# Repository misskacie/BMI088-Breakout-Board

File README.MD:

# Breakout Board for BMI088 Accelerometer/Gyroscrope
Provides breakouts for all pins, 2 headers for the I2C wires to allow daisy chaining, address selection jumper, mode select jumper, the option to bridge VDD and VDDIO as the supply voltage range overlaps for 3.3v logic level.

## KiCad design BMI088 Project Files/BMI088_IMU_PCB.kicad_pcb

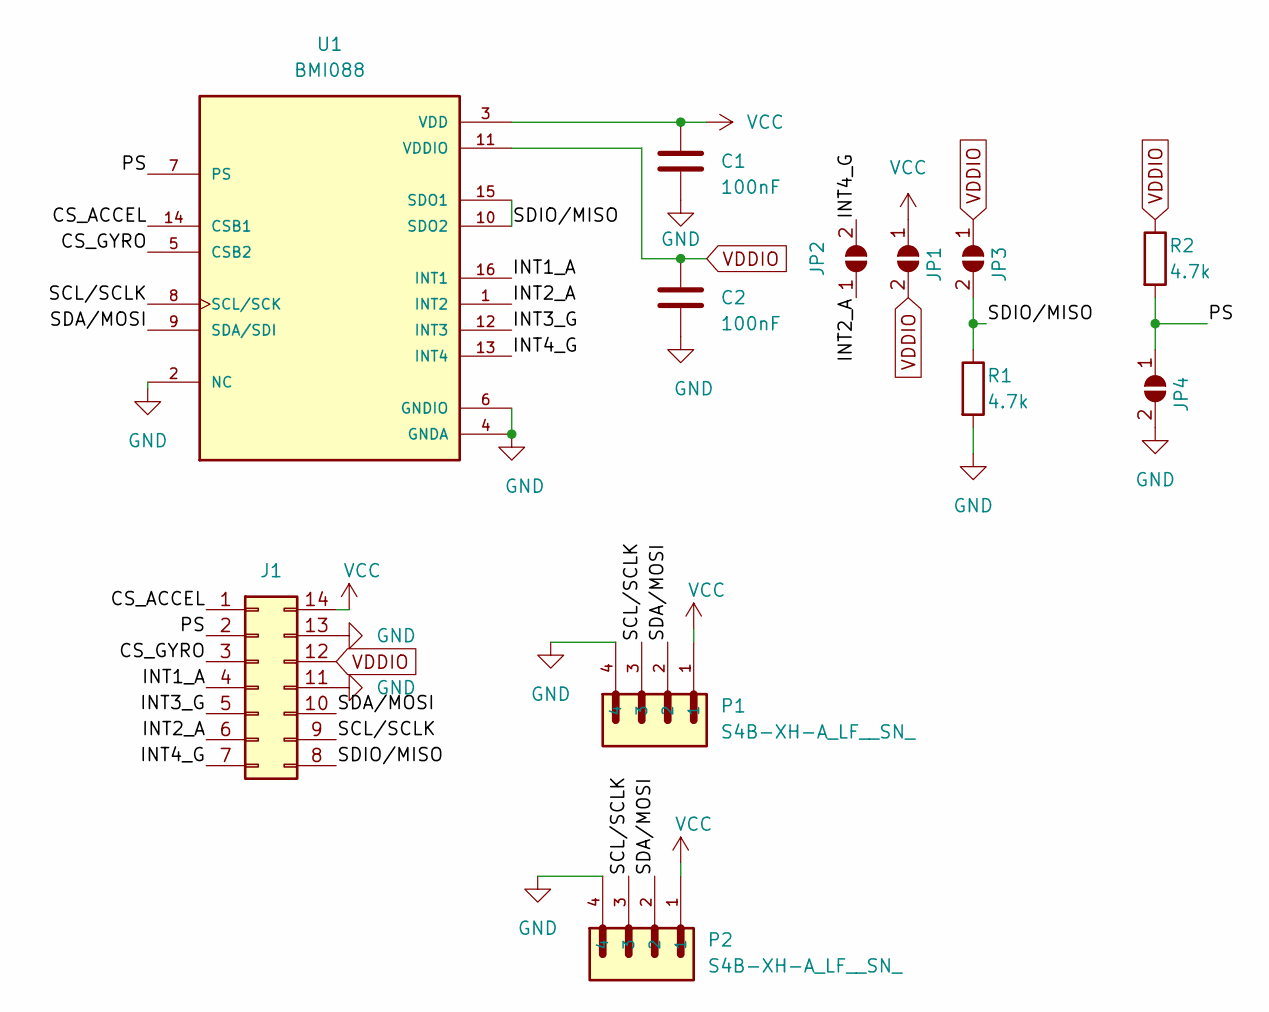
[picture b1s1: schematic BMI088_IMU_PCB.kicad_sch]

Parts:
C1, C2: 100nF; C_0603_1608Metric_Pad1.08x0.95mm_HandSolder
J1: Conn_02x07_Counter_Clockwise; PinSocket_2x07_P2.54mm_Vertical
JP1, JP2, JP3, JP4: SolderJumper_2_Open; SolderJumper-2_P1.3mm_Open_Pad1.0x1.5mm
P1, P2: S4B-XH-A_LF__SN_; JST_S4B-XH-A_LF__SN_
R1, R2: 4.7k; R_0603_1608Metric_Pad0.98x0.95mm_HandSolder
U1: BMI088; PQFN50P450X300X100-16N

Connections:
/CS_ACCEL: J1.1, U1.14 (CSB1)
/CS_GYRO: J1.3, U1.5 (CSB2)
/INT1_A: J1.4, U1.16 (INT1)
/INT2_A: J1.6, JP2.1 (A), U1.1 (INT2)
/INT3_G: J1.5, U1.12 (INT3)
/INT4_G: J1.7, JP2.2 (B), U1.13 (INT4)
/PS: J1.2, JP4.1 (A), R2.2, U1.7 (PS)
/SCL/SCLK: J1.9, P1.3, P2.3, U1.8 (SCL/SCK)
/SDA/MOSI: J1.10, P1.2, P2.2, U1.9 (SDA/SDI)
/SDIO/MISO: J1.8, JP3.2 (B), R1.1, U1.10 (SDO2), U1.15 (SDO1)
GND: C1.2, C2.2, J1.11, J1.13, JP4.2 (B), P1.4, P2.4, R1.2, U1.2 (NC), U1.4 (GNDA), U1.6 (GNDIO)
VCC: C1.1, J1.14, JP1.1 (A), P1.1, P2.1, U1.3 (VDD)
VDDIO: C2.1, J1.12, JP1.2 (B), JP3.1 (A), R2.1, U1.11 (VDDIO)

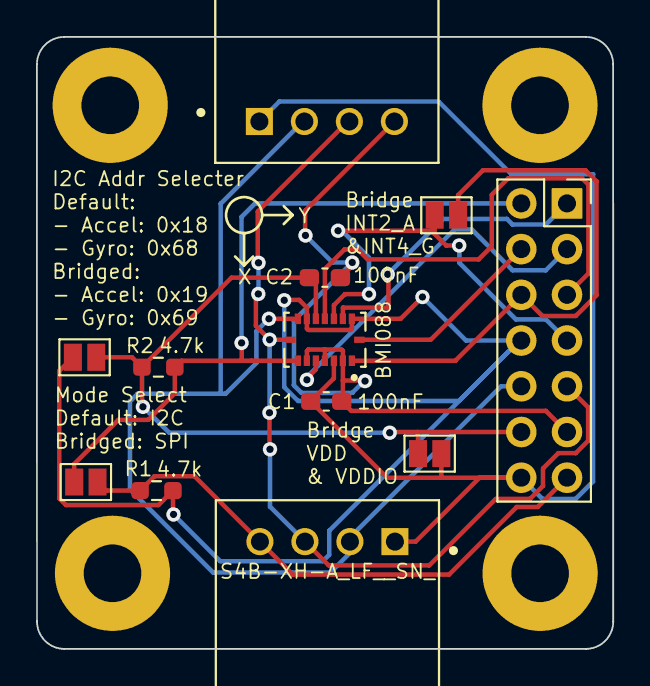
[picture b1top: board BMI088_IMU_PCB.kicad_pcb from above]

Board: 2 copper layers, 32.0 x 34.0 mm, 16 parts (0 on the bottom side), 13 nets.

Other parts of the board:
TH1, TH2, TH3, TH4: (no value)

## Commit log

2024-02-05 Finished Board
